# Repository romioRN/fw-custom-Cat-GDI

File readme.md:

See https://github.com/rusefi/rusefi/wiki/Custom-Firmware

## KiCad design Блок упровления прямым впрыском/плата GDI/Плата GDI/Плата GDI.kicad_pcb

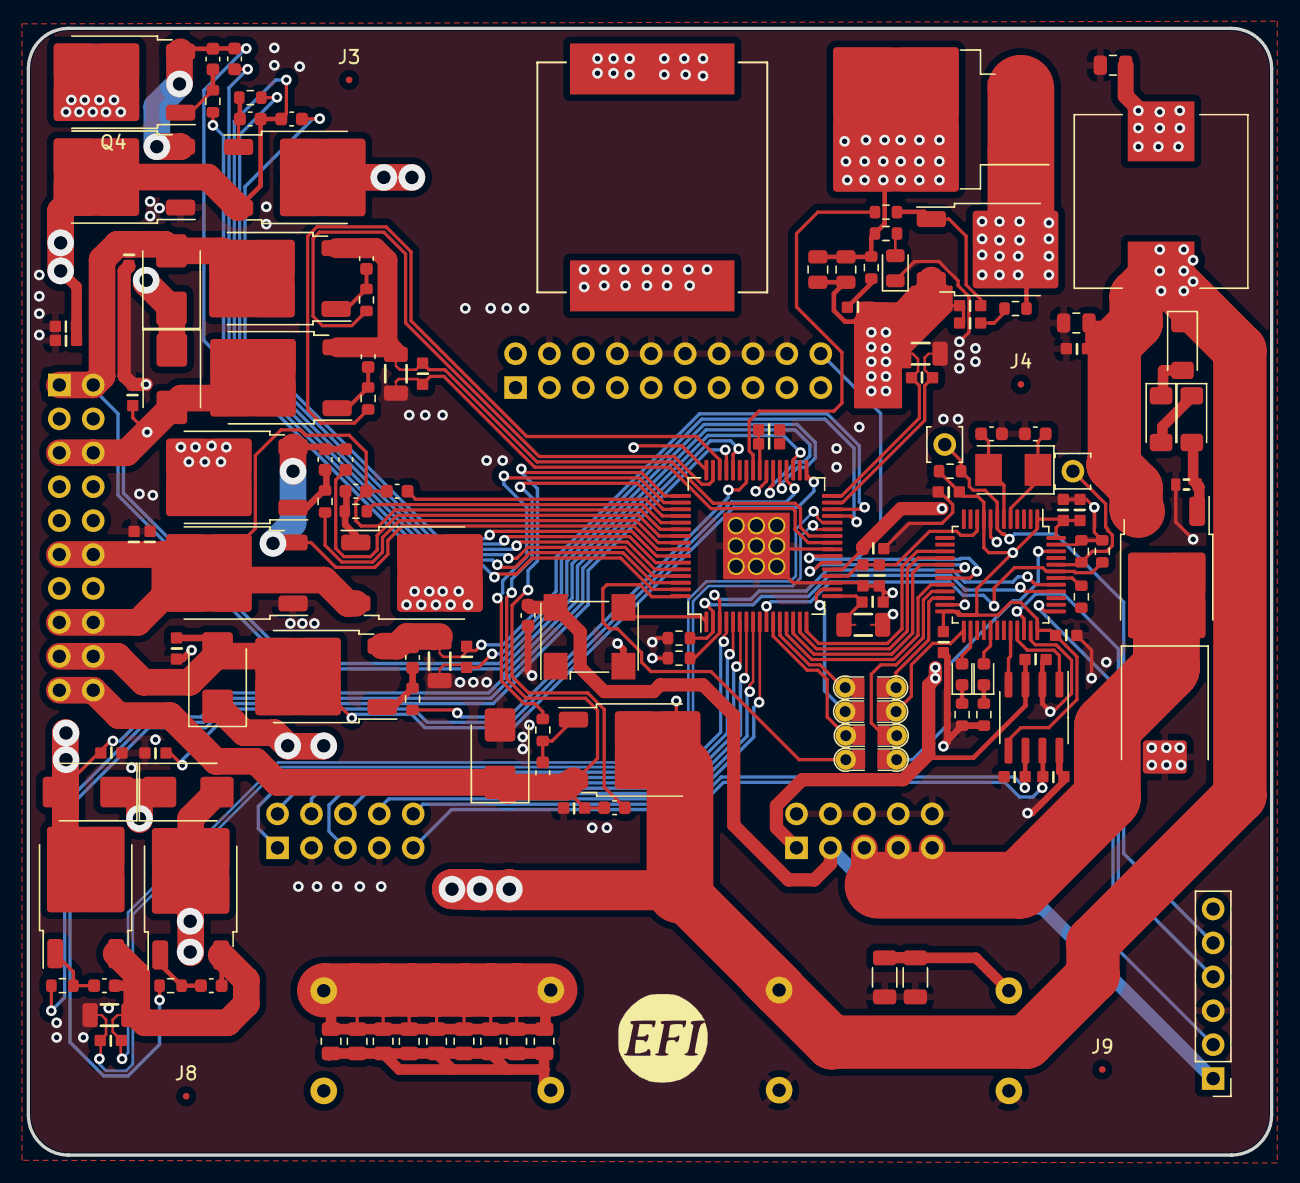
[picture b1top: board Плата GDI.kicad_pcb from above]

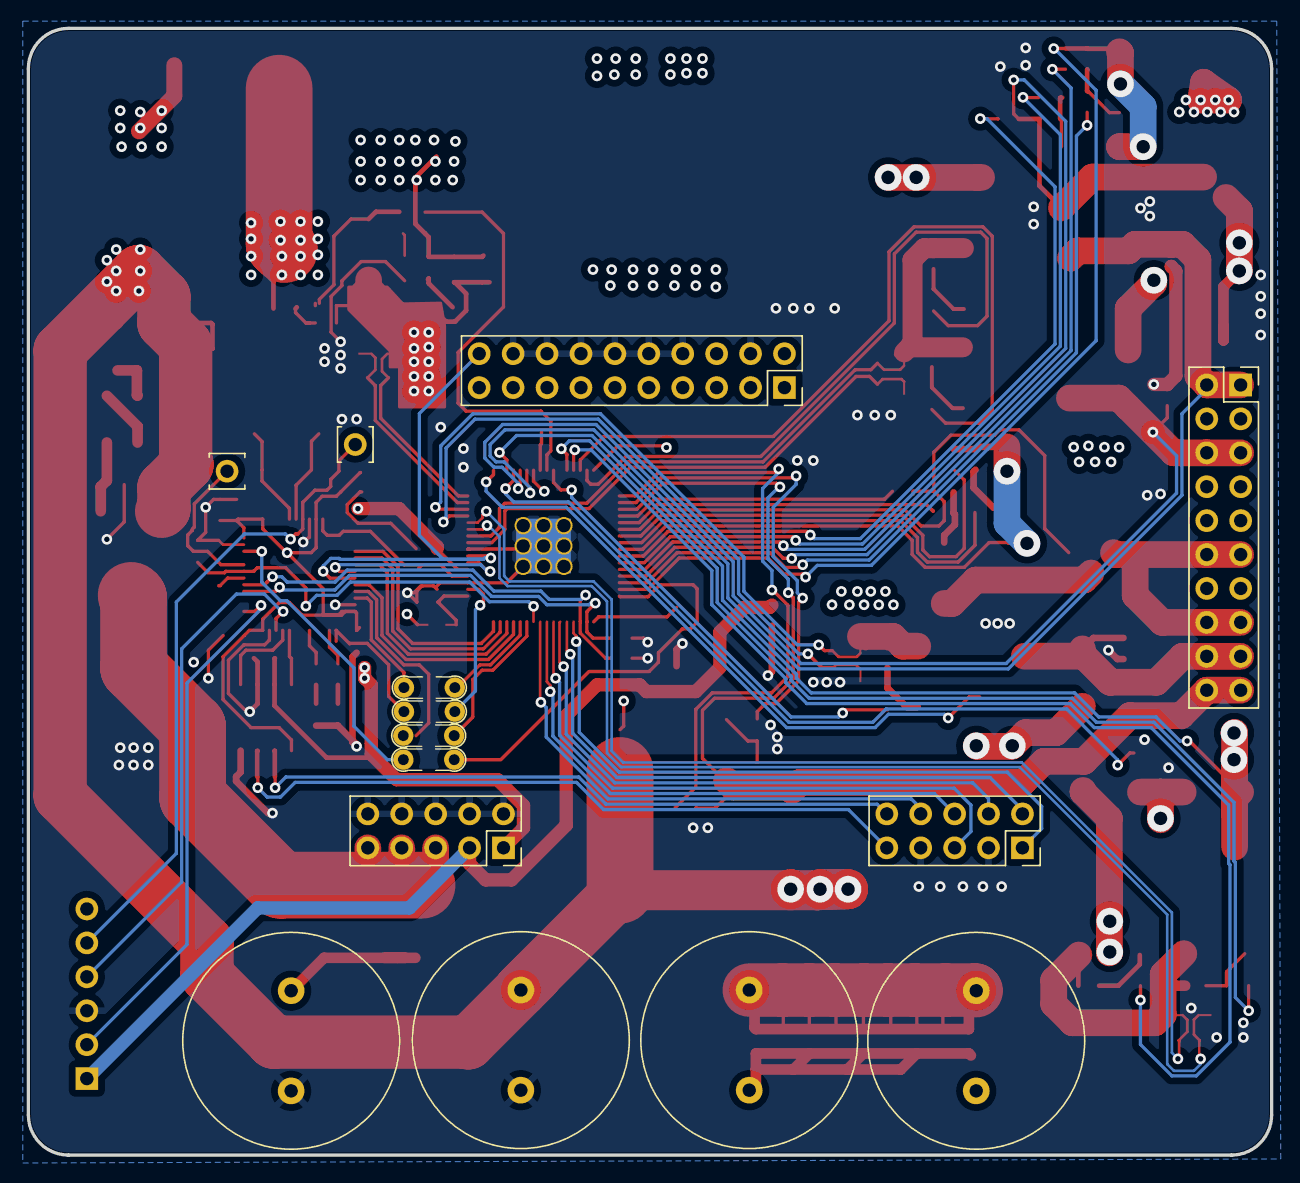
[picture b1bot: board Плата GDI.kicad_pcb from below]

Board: 4 copper layers, 93.1 x 84.4 mm, 148 parts (8 on the bottom side), 107 nets.

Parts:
C1, C2: 47p; C0603
C4, C73, C74, C75, C76, C78, C79, C82, C85, C87: 100n; C0603
C37, C38, C39, C40, C41, C42, C43, C44, C45, C47: 4700p; C0603
C49, C50: 18pF; C_0603_1608Metric
C52, C53, C54, C55, C56, C57, C58, C59, C60, C62, C91: 1000pF; C_0603_1608Metric
C64, C65, C67, C68, C70: 0.33uF; C_0603_1608Metric
C66, C69, C71, C77, C92, C93: 330p; C0603
C72, C80: 4.7u; C0603
C81, C88: 1200uF; C_Radial_D16.0mm_H25.0mm_P7.50mm
C84: 1u; C0603
C86, C90, C94, C96: 0.22uF; C_0805_2012Metric
C89: 470p; C0603
C95, C97: 470uF; C_Radial_D16.0mm_H25.0mm_P7.50mm
D1, D2, D3: ZMM5V6; D_MiniMELF
D4: SM15T33CA; D_SMC
D14, D15: SBR10200CTL; TO-252-2
D16, D17, D18, D19, D20, D22: STPS2H100UY; D_SMB
D24: RED; LED_0603_1608Metric
D25: GREEN; LED_0603_1608Metric
D26: SDURB1020CT; TO-263-2
D27: LED_Small; LED_0805_2012Metric
G1: RUSEFI_LOGO; rusefi_logo
J1: Conn_01x20; PinSocket_2x10_P2.54mm_Vertical
J2: Conn_02x10_Odd_Even; PinSocket_2x10_P2.54mm_Vertical
J3, J4, J8, J9: Conn_01x01; Fiducial_0.5mm_Mask1.5mm
J5: Conn_01x06; PinHeader_1x06_P2.54mm_Vertical
J6, J7: Conn_01x10; PinSocket_2x05_P2.54mm_Vertical
L1: 6.8uH; L_Wuerth_HCI-1350
L2: 10uH; L_Vishay_IHLP-6767
P1, P2: Pad; PAD-TH
Q1: AOD4185; TO-252-2
Q4, Q5, Q6, Q7, Q8, Q9, Q10, Q11, Q12, Q14, Q16: BUK9230-100B; TO-252-2
R1, R85: 10K; R_0603_1608Metric
R19: 10k; R0603
R86, R111, R116, R117, R118: 1K; R_0603_1608Metric
R87: 0; R_0603_1608Metric
R88, R89, R90, R119, R121: 0.01; Shunt_1206
R98, R99, R100, R101, R102, R103, R104, R105, R106, R108, R120: 10; R_0603_1608Metric
R112, R113, R114, R115: DNP; PAD-0805-PAD
R122: 220; R_0603_1608Metric
R123: 5.1; R_0603_1608Metric
R124, R126: 2K; R_1206_3216Metric
R125, R127, R128, R129, R130, R132, R133, R134, R135: 56k; R_0805_2012Metric
R131: 75K; R_0603_1608Metric
U1: TJA1051T-3; SOIC-8_3.9x4.9mm_P1.27mm
U7: STM32F103CBT6; LQFP-48_7x7mm_P0.5mm
U8: MC33PT2001AE; LQFP-64-1EP_10x10mm_P0.5mm_EP5x5mm_ThermalVias
Y2: 1MHz; Oscillator_SMD_Diodes_FN-4Pin_7.0x5.0mm
Y3: 8MHz; Crystal_SMD_5032-2Pin_5.0x3.2mm

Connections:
+3.3V: C72.2, C73.2, C74.2, C75.2, C79.2, C91.2, J5.1, J7.3, R1.1, R119.1, U1.5 (VIO), U7.1 (VBAT), U7.9 (VDDA), U7.24 (VDD), U7.36 (VDD), U7.48 (VDD), Y2.4 (VDD)
+5V: C4.2, C85.2, J7.1, U1.3 (VCC), U8.21 (VCC5)
+BATT: C76.2, C81.1, C86.1, D1.1 (K), D22.1 (K), L1.1, Q1.3 (S), Q4.2 (D), Q8.2 (D), Q12.2 (D), U8.39 (VBAT)
/+Batt_filtered: C88.1, C90.1, L1.2, L2.1, R124.1, R126.1
/Boot0: P2.1, R85.1, U7.44 (BOOT0)
/CAN_H: C1.1, J6.9, U1.7 (CANH)
/CAN_L: C2.2, J6.10, U1.6 (CANL)
/CAN_RX: U1.4 (RXD), U7.32 (PA11)
/CAN_TX: U1.1 (TXD), U7.33 (PA12)
/CLK: U8.1 (CLK), Y2.3 (RFout)
/CSB: U7.20 (PB2), U8.13 (CS)
/DBG: R115.2, U7.25 (PB12)
/DRVEN: R116.1, U7.40 (PB4), U8.2 (DRVEN)
/FLAG_0: R118.1, U7.43 (PB7), U8.10 (FLAG0)
/FLAG_1: R113.2, U7.21 (PB10)
/FLAG_2: R114.2, U7.22 (PB11)
/H1: C37.2, C38.2, C53.1, C65.2, D14.2 (K), J1.3, J1.4, J1.7, J1.8, Q5.3 (S), U8.60 (S_HS2)
/H3: C41.2, C42.2, C57.1, C68.2, D15.2 (K), J1.11, J1.12, J1.15, J1.16, Q9.3 (S), U8.54 (S_HS4)
/H5PUMP: C45.2, C60.1, C70.2, D20.1 (K), J1.19, J1.20, Q12.3 (S), U8.51 (S_HS5)
/IRQ: R112.2, U7.46 (PB9)
/L1: C39.2, D16.2 (A), J1.1, J1.2, Q6.2 (D), U8.38 (D_LS1)
/L2: C40.2, D17.2 (A), J1.5, J1.6, Q7.2 (D), U8.37 (D_LS2)
/L3: C43.2, D18.2 (A), J1.9, J1.10, Q10.2 (D), U8.36 (D_LS3)
/L4: C44.2, D19.2 (A), J1.13, J1.14, Q11.2 (D), U8.35 (D_LS4)
/L6PUMP: C47.2, D22.2 (A), J1.17, J1.18, Q14.2 (D), U8.33 (D_LS6)
/LED_GREEN: D25.2 (A), U7.29 (PA8)
/MISO: U7.16 (PA6), U8.15 (MISO)
/MOSI: U7.17 (PA7), U8.14 (MOSI)
/OA_1: U7.18 (PB0), U8.22 (OA_1)
/OA_2: J2.20, U7.19 (PB1), U8.23 (OA_2)
/RESETB: R117.1, U7.41 (PB5), U8.3 (RESET)
/SCLK: U7.15 (PA5), U8.16 (SCK)
/START1: J6.1, U8.4 (START1)
/START2: J6.2, U8.5 (START2)
/START3: J6.4, U8.6 (START3)
/START4: J6.5, U8.7 (START4)
/START5: J6.6, U8.8 (START5)
/START6: J6.8, U8.9 (START6)
/SWCLK: J5.2, U7.37 (PA14)
/SWDIO: J5.4, U7.34 (PA13)
/UART_RX: J2.2, U7.31 (PA10)
/UART_TX: J2.6, U7.30 (PA9)
/VCC2P5: C82.2, C84.2, U7.10 (PA0), U8.20 (VCC2P5)
/VCCP: C78.2, C80.2, U8.40 (VCCP)
/VSENSE1: C54.1, C55.1, Q6.3 (S), Q7.3 (S), R88.1
/VSENSE2: C58.1, C59.1, Q10.3 (S), Q11.3 (S), R89.1
/Vdrive_coil: D26.1 (A), D26.3 (A), L2.2, Q16.2 (D), R122.2
/Vdrive_shunt: C89.1, C92.1, C93.1, C94.2, C95.2, C96.2, C97.2, Q16.3 (S), R121.1, R125.2, R127.2, R128.2, R129.2, R130.2, R132.2, R133.2, R134.2, R135.2
/nRESET: J5.5, P1.1, R1.2, U7.7 (NRST)
GND: C1.2, C2.1, C4.1, C37.1, C38.1, C39.1, C40.1, C41.1, C42.1, C43.1, C44.1, C45.1, C47.1, C49.2, C50.2, C72.1, C73.1, C74.1, C75.1, C76.1, C78.1, C79.1, C80.1, C81.2, C82.1, C84.1, C85.1, C86.2, C87.1, C88.2, C90.2, C91.1, D4.2 (A2), D14.1 (A), D15.1 (A), D20.2 (A), D27.1 (K), J2.4, J2.8, J2.10, J2.12, J2.14, J2.16, J2.18, J5.3, J6.3, J6.7, J7.2, J7.4, J7.6, J7.8, J7.10, R19.1, R85.2, R86.2, R88.4, R89.4, R90.4, R111.1, R116.2, R117.2, R118.2, R121.4, R124.2, R126.2, U1.2 (GND), U1.8 (S), U7.8 (VSSA), U7.23 (VSS), U7.35 (VSS), U7.47 (VSS), U8.19 (DGND), U8.24 (AGND), U8.65 (PGND), Y2.2 (GND)
unnamed: C92.2, R122.1
unnamed: C93.2, R123.1
unnamed: D1.2 (A), D2.1 (K)
unnamed: D2.2 (A), D3.1 (K)
unnamed: D3.2 (A), Q1.1 (G), R19.2
unnamed: D4.1 (A1), J7.5, J7.7, J7.9, Q1.2 (D)
unnamed: D24.2 (A), U7.26 (PB13)
unnamed: D24.1 (K), R86.1
unnamed: D25.1 (K), R111.2
unnamed: D27.2 (A), R131.1
unnamed: C52.2, Q4.1 (G), R98.2
unnamed: C52.1, C64.2, D14.3 (A), Q4.3 (S), U8.63 (S_HS1)
unnamed: C53.2, Q5.1 (G), R99.2
unnamed: C54.2, Q6.1 (G), R100.2
unnamed: C55.2, Q7.1 (G), R101.2
unnamed: C56.2, Q8.1 (G), R102.2
unnamed: C56.1, C67.2, D15.3 (A), Q8.3 (S), U8.57 (S_HS3)
unnamed: C57.2, Q9.1 (G), R103.2
unnamed: C58.2, Q10.1 (G), R104.2
unnamed: C59.2, Q11.1 (G), R105.2
unnamed: C60.2, Q12.1 (G), R106.2
unnamed: C62.2, Q14.1 (G), R108.2
unnamed: C62.1, Q14.3 (S), R90.1
unnamed: C89.2, Q16.1 (G), R120.1
unnamed: R87.2, U7.42 (PB6)
unnamed: C49.1, U7.5 (PD0), Y3.1
unnamed: C50.1, U7.6 (PD1), Y3.2
unnamed: C64.1, U8.61 (B_HS1)
unnamed: C65.1, U8.58 (B_HS2)
unnamed: C67.1, U8.55 (B_HS3)
unnamed: C68.1, U8.52 (B_HS4)
unnamed: C70.1, U8.49 (B_HS5)
unnamed: R115.1, U8.18 (DBG)
unnamed: R113.1, U8.11 (FLAG1)
unnamed: R114.1, U8.12 (FLAG2)
unnamed: R98.1, U8.62 (G_HS1)
unnamed: R99.1, U8.59 (G_HS2)
unnamed: R102.1, U8.56 (G_HS3)
unnamed: R103.1, U8.53 (G_HS4)
unnamed: R106.1, U8.50 (G_HS5)
unnamed: R100.1, U8.47 (G_LS1)
unnamed: R101.1, U8.46 (G_LS2)
unnamed: R104.1, U8.45 (G_LS3)
unnamed: R105.1, U8.44 (G_LS4)
unnamed: R108.1, U8.42 (G_LS6)
unnamed: R120.2, U8.41 (G_LS7)
unnamed: R112.1, U8.64 (IRQ)
unnamed: C87.2, R119.4, U8.17 (VCCIO)
unnamed: C66.1, R88.3, U8.25 (VSENSEN1)
unnamed: C69.1, R89.3, U8.27 (VSENSEN2)
unnamed: C71.1, R90.3, U8.29 (VSENSEN3)
unnamed: C77.1, R121.3, U8.31 (VSENSEN4)
unnamed: C66.2, R88.2, U8.26 (VSENSEP1)
unnamed: C69.2, R89.2, U8.28 (VSENSEP2)
unnamed: C71.2, R90.2, U8.30 (VSENSEP3)
unnamed: C77.2, R121.2, U8.32 (VSENSEP4)
Vdrive: C94.1, C95.1, C96.1, C97.1, D16.1 (K), D17.1 (K), D18.1 (K), D19.1 (K), D26.2 (K), Q5.2 (D), Q9.2 (D), R123.2, R125.1, R127.1, R128.1, R129.1, R130.1, R131.2, R132.1, R133.1, R134.1, R135.1, U8.48 (VBOOST)

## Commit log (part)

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2025-10-08 GHA says update ext/rusefi submodule
